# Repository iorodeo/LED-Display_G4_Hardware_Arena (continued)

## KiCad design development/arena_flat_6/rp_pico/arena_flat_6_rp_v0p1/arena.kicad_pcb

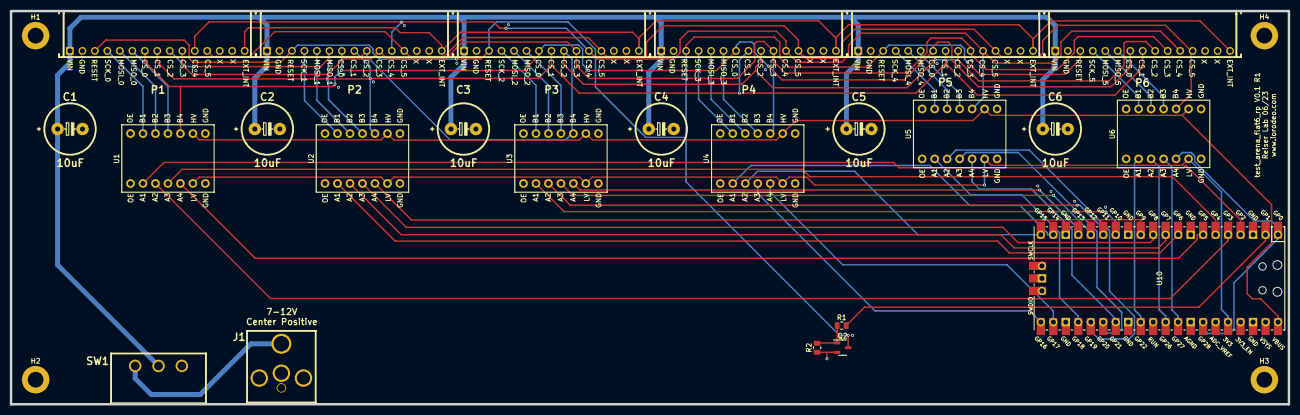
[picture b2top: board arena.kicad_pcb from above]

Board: 4 copper layers, 260.0 x 80.0 mm, 28 parts (0 on the bottom side), 57 nets.

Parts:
C1, C2, C3, C4, C5, C6: 10uF; Capacitor_Polarized
H1, H2, H3, H4: MountingHole_Pad; MountingHole_3.2mm_M3_DIN965_Pad
J1: Barrel_Jack; DCJACK_2PIN_HIGHCURRENT
P1, P2, P3, P4, P5, P6: CONN15; HEADER_TOP
Q2: MOSFET_NCHAN; SOT-23-3
R1: 200; R_0805_2012Metric
R2: 20k; R_0805_2012Metric
SW1: SW_SPDT; slide_switch
U1, U2, U3, U4, U5, U6: SPARKFUN_TXB0104
U10: Pico; RPi_Pico_SMD_TH

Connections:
/3V3: U1.6 (LV), U2.6 (LV), U3.6 (LV), U4.6 (LV), U5.6 (LV), U6.6 (LV), U10.36 (3V3)
/5V: U1.9 (HV), U2.9 (HV), U3.9 (HV), U4.9 (HV), U5.9 (HV), U6.9 (HV), U10.40 (VBUS)
/CS_0_3V3: U1.5 (A4), U10.7 (GPIO5)
/CS_0_5V: P1.7, P2.7, P3.7, P4.7, P5.7, P6.7, U1.10 (B4)
/CS_1_3V3: U2.5 (A4), U10.12 (GPIO9)
/CS_1_5V: P1.8, P2.8, P3.8, P4.8, P5.8, P6.8, U2.10 (B4)
/CS_2_3V3: U3.5 (A4), U10.17 (GPIO13)
/CS_2_5V: P1.9, P2.9, P3.9, P4.9, P5.9, P6.9, U3.10 (B4)
/CS_3_3V3: U4.5 (A4), U10.22 (GPIO17)
/CS_3_5V: P1.10, P2.10, P3.10, P4.10, P5.10, P6.10, U4.10 (B4)
/CS_4_3V3: U5.5 (A4), U10.27 (GPIO21)
/CS_4_5V: P1.11, P2.11, P3.11, P4.11, P5.11, P6.11, U5.10 (B4)
/CS_5_3V3: U6.5 (A4), U10.1 (GPIO0), U10.34 (GPIO28_ADC2)
/CS_5_5V: P1.12, P2.12, P3.12, P4.12, P5.12, P6.12, U6.10 (B4)
/EXT_INT_5V: P1.15, P2.15, P3.15, P4.15, P5.15, P6.15
/MISO_0_3V3: U1.4 (A3), U10.6 (GPIO4)
/MISO_0_5V: P1.6, U1.11 (B3)
/MISO_1_3V3: U2.4 (A3), U10.11 (GPIO8)
/MISO_1_5V: P2.6, U2.11 (B3)
/MISO_2_3V3: U3.4 (A3), U10.16 (GPIO12)
/MISO_2_5V: P3.6, U3.11 (B3)
/MISO_3_3V3: U4.4 (A3), U10.21 (GPIO16)
/MISO_3_5V: P4.6, U4.11 (B3)
/MISO_4_3V3: U5.4 (A3), U10.26 (GPIO20)
/MISO_4_5V: P5.6, U5.11 (B3)
/MISO_5_3V3: U6.4 (A3), U10.32 (GPIO27_ADC1)
/MISO_5_5V: P6.6, U6.11 (B3)
/MOSI_0_3V3: U1.3 (A2), U10.5 (GPIO3)
/MOSI_0_5V: P1.5, U1.12 (B2)
/MOSI_1_3V3: U2.3 (A2), U10.10 (GPIO7)
/MOSI_1_5V: P2.5, U2.12 (B2)
/MOSI_2_3V3: U3.3 (A2), U10.15 (GPIO11)
/MOSI_2_5V: P3.5, U3.12 (B2)
/MOSI_3_3V3: U4.3 (A2), U10.20 (GPIO15)
/MOSI_3_5V: P4.5, U4.12 (B2)
/MOSI_4_3V3: U5.3 (A2), U10.25 (GPIO19)
/MOSI_4_5V: P5.5, U5.12 (B2)
/MOSI_5_3V3: U6.3 (A2), U10.31 (GPIO26_ADC0)
/MOSI_5_5V: P6.5, U6.12 (B2)
/RESET: R1.2, U10.2 (GPIO1)
/RESET_PAN: P1.3, P2.3, P3.3, P4.3, P5.3, P6.3, Q2.3 (D)
/SCK_0_3V3: U1.2 (A1), U10.4 (GPIO2)
/SCK_0_5V: P1.4, U1.13 (B1)
/SCK_1_3V3: U2.2 (A1), U10.9 (GPIO6)
/SCK_1_5V: P2.4, U2.13 (B1)
/SCK_2_3V3: U3.2 (A1), U10.14 (GPIO10)
/SCK_2_5V: P3.4, U3.13 (B1)
/SCK_3_3V3: U4.2 (A1), U10.19 (GPIO14)
/SCK_3_5V: P4.4, U4.13 (B1)
/SCK_4_3V3: U5.2 (A1), U10.24 (GPIO18)
/SCK_4_5V: P5.4, U5.13 (B1)
/SCK_5_3V3: U6.2 (A1), U10.29 (GPIO22)
/SCK_5_5V: P6.4, U6.13 (B1)
/VIN: C1.1, C2.1, C3.1, C4.1, C5.1, C6.1, P1.1, P2.1, P3.1, P4.1, P5.1, P6.1, SW1.2 (B)
/VIN_SW: J1.1, SW1.1 (A)
GND: C1.2, C2.2, C3.2, C4.2, C5.2, C6.2, H1.1, H2.1, H3.1, H4.1, J1.2, P1.2, P2.2, P3.2, P4.2, P5.2, P6.2, Q2.2 (S), R2.1, SW1.3 (C), U1.7 (GND), U1.8 (GND), U2.7 (GND), U2.8 (GND), U3.7 (GND), U3.8 (GND), U4.7 (GND), U4.8 (GND), U5.7 (GND), U5.8 (GND), U6.7 (GND), U6.8 (GND), U10.3 (GND), U10.8 (GND), U10.13 (GND), U10.18 (GND), U10.23 (GND), U10.28 (GND), U10.33 (AGND), U10.38 (GND), U10.42 (GND)
unnamed: Q2.1 (G), R1.1, R2.2

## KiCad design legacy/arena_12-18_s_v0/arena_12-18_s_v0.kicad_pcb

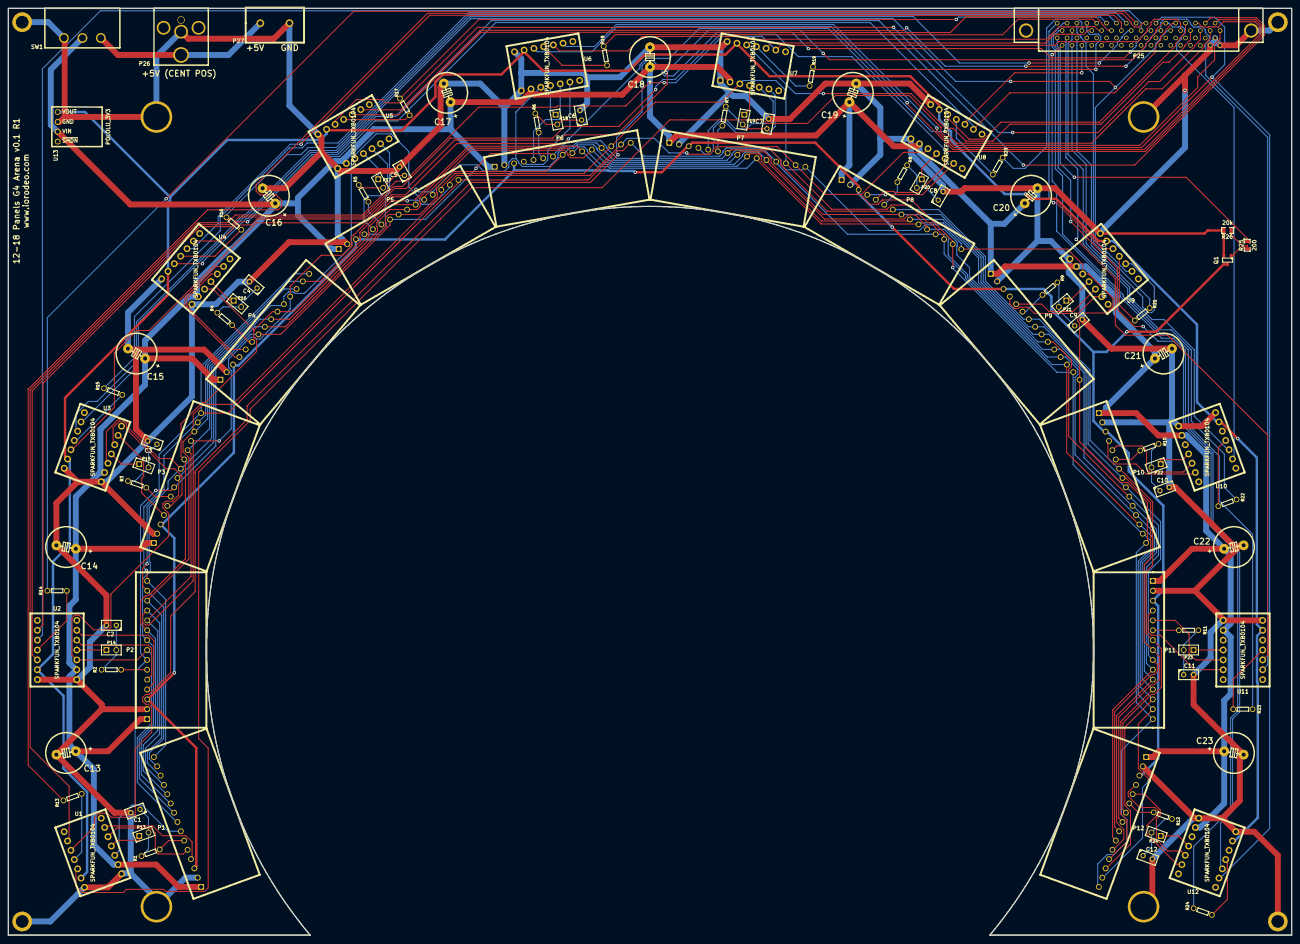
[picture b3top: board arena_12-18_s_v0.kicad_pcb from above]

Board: 2 copper layers, 330.2 x 238.5 mm, 99 parts (0 on the bottom side), 127 nets.

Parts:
C1, C2, C3, C4, C5, C6, C7, C8, C9, C10, C11, C12: C; C1
C13, C14, C15, C16, C17, C19, C20, C21, C22, C23: 10uF; Capacitor_Polarized
C18: 10uf; Capacitor_Polarized
P1, P2, P3, P4, P5, P6, P7, P8, P9, P10, P11, P12: CONN15; PANEL_G4
P13, P14, P15, P16, P17, P18, P19, P20, P21, P22, P23, P24: CONN_2; PIN_ARRAY_2X1
P25: CONN_34X2; TE_CONN_DSUB_RA_68
P26: CONN_2; DCJACK_2PIN_HIGHCURRENT
P27: CONN_2; TERM_7P5MM
P28, P29, P30, P31: CONN_1; 0P25_MOUNT_HOLE
P32, P33, P34, P35: CONN_1; #4_THROUGH_HOLE
Q1: MOSFET_NCHAN; SOT23
R1, R2, R3, R4, R5, R6, R7, R8, R9, R10, R11, R12, R13, R14, R15, R16, R17, R18, R19, R20, R21, R22, R23, R24: R; R_SMALL
R25: 200; SM0805
R26: 20k; SM0805
SW1: SWITCH_INV; slide_switch
U1, U2, U3, U4, U5, U6, U7, U8, U9, U10, U11, U12: SPARKFUN_TXB0104
U13: POLOLU_3V3

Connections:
+5V: P26.1, P27.1, SW1.1
/3V3: U1.6, U2.6, U3.6, U4.6, U5.6, U6.6, U7.6, U8.6, U9.6, U10.6, U11.6, U12.6, U13.4
/5V: C13.1, C14.1, C15.1, C16.1, C17.1, C18.1, C19.1, C20.1, C21.1, C22.1, C23.1, P1.1, P2.1, P3.1, P4.1, P5.1, P6.1, P7.1, P8.1, P9.1, P10.1, P11.1, P12.1, SW1.2, U1.9, U2.9, U3.9, U4.9, U5.9, U6.9, U7.9, U8.9, U9.9, U10.9, U11.9, U12.9, U13.2
/CS_0_3V3: P25.35, U1.5
/CS_0_5V: P1.7, P2.7, P3.7, P4.7, P5.7, P6.7, P7.7, P8.7, P9.7, P10.7, P11.7, P12.7, U1.10
/CS_1_3V3: P25.36, U2.5
/CS_1_5V: P1.8, P2.8, P3.8, P4.8, P5.8, P6.8, P7.8, P8.8, P9.8, P10.8, P11.8, P12.8, U2.10
/CS_2_3V3: P25.37, U3.5
/CS_2_5V: P1.9, P2.9, P3.9, P4.9, P5.9, P6.9, P7.9, P8.9, P9.9, P10.9, P11.9, P12.9, U3.10
/CS_3_3V3: P25.38, U4.5
/CS_3_5V: P1.10, P2.10, P3.10, P4.10, P5.10, P6.10, P7.10, P8.10, P9.10, P10.10, P11.10, P12.10, U4.10
/CS_4_3V3: P25.39, U5.5
/CS_4_5V: P1.11, P2.11, P3.11, P4.11, P5.11, P6.11, P7.11, P8.11, P9.11, P10.11, P11.11, P12.11, U5.10
/CS_5_3V3: P25.40, U6.5
/CS_5_5V: P1.12, P2.12, P3.12, P4.12, P5.12, P6.12, P7.12, P8.12, P9.12, P10.12, P11.12, P12.12, U6.10
/CS_6_3V3: P25.41, U7.5
/CS_6_5V: P1.13, P2.13, P3.13, P4.13, P5.13, P6.13, P7.13, P8.13, P9.13, P10.13, P11.13, P12.13, U7.10
/CS_7_3V3: P25.42, U8.5
/CS_7_5V: P1.14, P2.14, P3.14, P4.14, P5.14, P6.14, P7.14, P8.14, P9.14, P10.14, P11.14, P12.14, U8.10
/EXT_INT_3V3: P25.68, U9.5
/EXT_INT_5V: P1.15, P2.15, P3.15, P4.15, P5.15, P6.15, P7.15, P8.15, P9.15, P10.15, P11.15, P12.15, U9.10
/MISO_0_3V3: P25.50, R13.2
/MISO_0_5V: P1.6, R1.1
/MISO_1_3V3: P25.52, R14.2
/MISO_1_5V: P2.6, R2.1
/MISO_2_3V3: P25.54, R15.2
/MISO_2_5V: P3.6, R3.1
/MISO_3_3V3: P25.56, R16.2
/MISO_3_5V: P4.6, R4.1
/MISO_4_3V3: P25.58, R17.2
/MISO_4_5V: P5.6, R5.1
/MISO_5_3V3: P25.60, R18.2
/MISO_5_5V: P6.6, R6.1
/MISO_6_3V3: P25.62, R19.2
/MISO_6_5V: P7.6, R7.1
/MISO_7_3V3: P25.63, R20.2
/MISO_7_5V: P8.6, R8.1
/MISO_8_3V3: P25.64, R21.2
/MISO_8_5V: P9.6, R9.1
/MISO_9_3V3: P25.65, R22.2
/MISO_9_5V: P10.6, R10.1
/MISO_10_3V3: P25.66, R23.2
/MISO_10_5V: P11.6, R11.1
/MISO_11_3V3: P25.67, R24.2
/MISO_11_5V: P12.6, R12.1
/MOSI_0_3V3: P25.49, U1.3
/MOSI_0_5V: P1.5, U1.12
/MOSI_1_3V3: P25.51, U2.3
/MOSI_1_5V: P2.5, U2.12
/MOSI_2_3V3: P25.53, U3.3
/MOSI_2_5V: P3.5, U3.12
/MOSI_3_3V3: P25.55, U4.3
/MOSI_3_5V: P4.5, U4.12
/MOSI_4_3V3: P25.57, U5.3
/MOSI_4_5V: P5.5, U5.12
/MOSI_5_3V3: P25.59, U6.3
/MOSI_5_5V: P6.5, U6.12
/MOSI_6_3V3: P25.61, U7.3
/MOSI_6_5V: P7.5, U7.12
/MOSI_7_3V3: P25.29, U8.3
/MOSI_7_5V: P8.5, U8.12
/MOSI_8_3V3: P25.30, U9.3
/MOSI_8_5V: P9.5, U9.12
/MOSI_9_3V3: P25.31, U10.3
/MOSI_9_5V: P10.5, U10.12
/MOSI_10_3V3: P25.32, U11.3
/MOSI_10_5V: P11.5, U11.12
/MOSI_11_3V3: P25.33, U12.3
/MOSI_11_5V: P12.5, U12.12
/RESET: P25.34, R25.1
/RESET_PAN: P1.3, P2.3, P3.3, P4.3, P5.3, P6.3, P7.3, P8.3, P9.3, P10.3, P11.3, P12.3, Q1.3
/SCK_0_3V3: P25.43, U1.2, U7.2
/SCK_0_5V: P1.4, U1.13
/SCK_1_3V3: P25.44, U2.2, U8.2
/SCK_1_5V: P2.4, U2.13
/SCK_2_3V3: P25.45, U3.2, U9.2
/SCK_2_5V: P3.4, U3.13
/SCK_3_3V3: P25.46, U4.2, U10.2
/SCK_3_5V: P4.4, U4.13
/SCK_4_3V3: P25.47, U5.2, U11.2
/SCK_4_5V: P5.4, U5.13
/SCK_5_3V3: P25.48, U6.2, U12.2
/SCK_5_5V: P6.4, U6.13
/SCK_6_5V: P7.4, U7.13
/SCK_7_5V: P8.4, U8.13
/SCK_8_5V: P9.4, U9.13
/SCK_9_5V: P10.4, U10.13
/SCK_10_5V: P11.4, U11.13
/SCK_11_5V: P12.4, U12.13
GND: C1.2, C2.2, C3.2, C4.2, C5.2, C6.2, C7.2, C8.2, C9.2, C10.2, C11.2, C12.2, C13.2, C14.2, C15.2, C16.2, C17.2, C18.2, C19.2, C20.2, C21.2, C22.2, C23.2, P1.2, P2.2, P3.2, P4.2, P5.2, P6.2, P7.2, P8.2, P9.2, P10.2, P11.2, P12.2, P25.1, P25.2, P25.3, P25.69, P26.2, P27.2, P28.1, P29.1, P30.1, P31.1, P32.1, P33.1, P34.1, P35.1, Q1.2, R26.2, SW1.3, U1.7, U1.8, U2.7, U2.8, U3.7, U3.8, U4.7, U4.8, U5.7, U5.8, U6.7, U6.8, U7.7, U7.8, U8.7, U8.8, U9.7, U9.8, U10.7, U10.8, U11.7, U11.8, U12.7, U12.8, U13.3
unnamed: R21.1, U9.4
unnamed: R22.1, U10.4
unnamed: R19.1, U7.4
unnamed: R18.1, U6.4
unnamed: R20.1, U8.4
unnamed: C12.1, P24.2, R12.2
unnamed: C11.1, P23.2, R11.2
unnamed: P22.1, U10.11
unnamed: P21.1, U9.11
unnamed: P20.1, U8.11
unnamed: P19.1, U7.11
unnamed: P18.1, U6.11
unnamed: P17.1, U5.11
unnamed: C10.1, P22.2, R10.2
unnamed: P16.1, U4.11
unnamed: P15.1, U3.11
unnamed: P14.1, U2.11
unnamed: P13.1, U1.11
unnamed: C7.1, P19.2, R7.2
unnamed: C6.1, P18.2, R6.2
unnamed: C5.1, P17.2, R5.2
unnamed: C9.1, P21.2, R9.2
unnamed: P23.1, U11.11
unnamed: C8.1, P20.2, R8.2
unnamed: P24.1, U12.11
unnamed: R23.1, U11.4
unnamed: C2.1, P14.2, R2.2
unnamed: C1.1, P13.2, R1.2
unnamed: C4.1, P16.2, R4.2
unnamed: C3.1, P15.2, R3.2
unnamed: R24.1, U12.4
unnamed: R15.1, U3.4
unnamed: R14.1, U2.4
unnamed: R16.1, U4.4
unnamed: R17.1, U5.4
unnamed: R13.1, U1.4
unnamed: Q1.1, R25.2, R26.1
